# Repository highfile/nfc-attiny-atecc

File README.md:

# nfc-attiny-atecc
Secure element enabled nfc tag, inspired by the SiLo concept of Kong Cash

* NFC: NXP NTAG I2C plus
* Microcontroller: Attiny85V
* Secure Element: ATECC608A

Other than the microcontroller, the primary components are the same as used in Kong Cash. The assumption here (since their design is not open source) is that the mcu acts as a pass-through and doesn't require any special security features itself. All parts on this board are SOIC8 package for ease of hand soldered assembly, but all come in smaller QFN or similar packages for reduced size design.

**Update: Boards sent off for manufacture 3/4/20, COVID-19 likely to cause delays. Firmware to follow.**

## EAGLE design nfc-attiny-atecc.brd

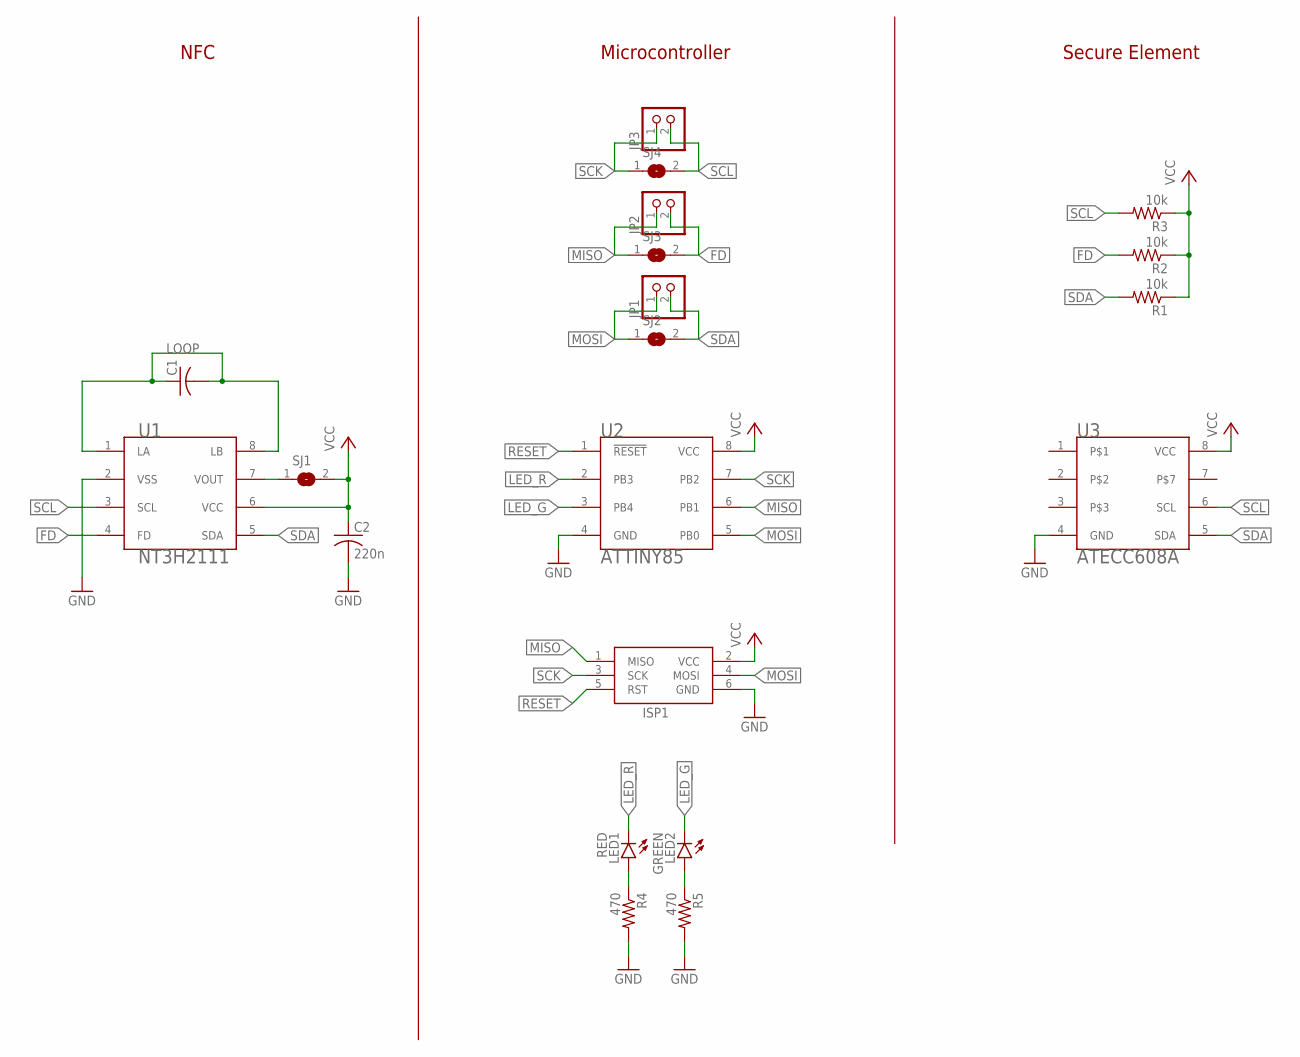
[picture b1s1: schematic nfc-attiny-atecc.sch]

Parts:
C1: C-USC0805; C0805
C2: 220n; C0805
ISP1: AVRISP-BOX
JP1, JP2, JP3: PINHD-1X2; 1X02
LED1: RED; CHIP-LED0805
LED2: GREEN; CHIP-LED0805
R1, R2, R3: 10k; R0805
R4, R5: 470; R0805
SJ1, SJ2, SJ3, SJ4: SJ
U1: NT3H2111; SOIC127P600X175-8N
U2: ATTINY85; SOIC127P797X215-8N
U3: ATECC608A; SOIC127P600X175-8N

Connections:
FD: JP2.2, R2.2, SJ3.2, U1.4 (FD)
GND: C2.2, ISP1.6 (GND), R4.2, R5.2, U1.2 (VSS), U2.4 (GND), U3.4 (GND)
LED_G: LED2.C, U2.3 (PB4)
LED_R: LED1.C, U2.2 (PB3)
LOOP: C1.1, C1.2, U1.1 (LA), U1.8 (LB)
MISO: ISP1.1 (MISO), JP2.1, SJ3.1, U2.6 (PB1)
MOSI: ISP1.4 (MOSI), JP1.1, SJ2.1, U2.5 (PB0)
unnamed: SJ1.1, U1.7 (VOUT)
unnamed: LED1.A, R4.1
unnamed: LED2.A, R5.1
RESET: ISP1.5 (RST), U2.1 (!RESET)
SCK: ISP1.3 (SCK), JP3.1, SJ4.1, U2.7 (PB2)
SCL: JP3.2, R3.2, SJ4.2, U1.3 (SCL), U3.6 (SCL)
SDA: JP1.2, R1.2, SJ2.2, U1.5 (SDA), U3.5 (SDA)
VCC: C2.1, ISP1.2 (VCC), R1.1, R2.1, R3.1, SJ1.2, U1.6 (VCC), U2.8 (VCC), U3.8 (VCC)

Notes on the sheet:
NFC
Microcontroller
Secure Element

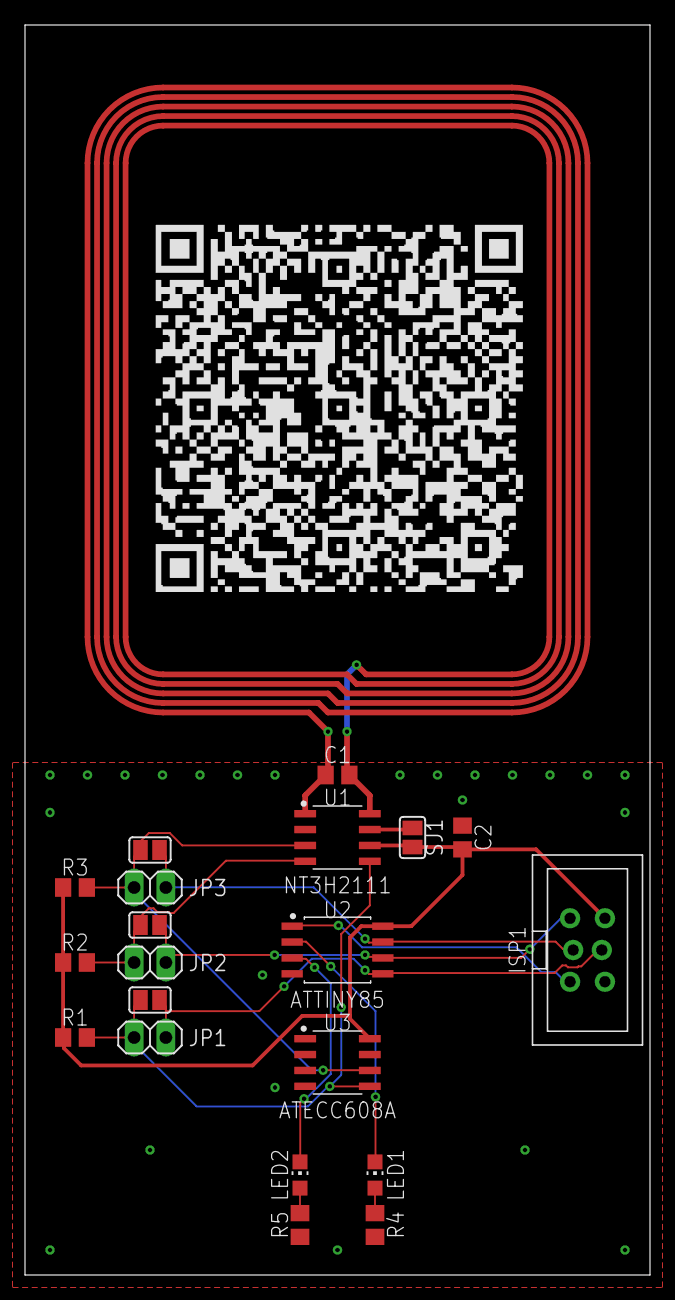
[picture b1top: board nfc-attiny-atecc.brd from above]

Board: 2 copper layers, 50.0 x 100.0 mm, 20 parts (0 on the bottom side), 15 nets.

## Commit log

2020-03-04 update readme, add antenna
